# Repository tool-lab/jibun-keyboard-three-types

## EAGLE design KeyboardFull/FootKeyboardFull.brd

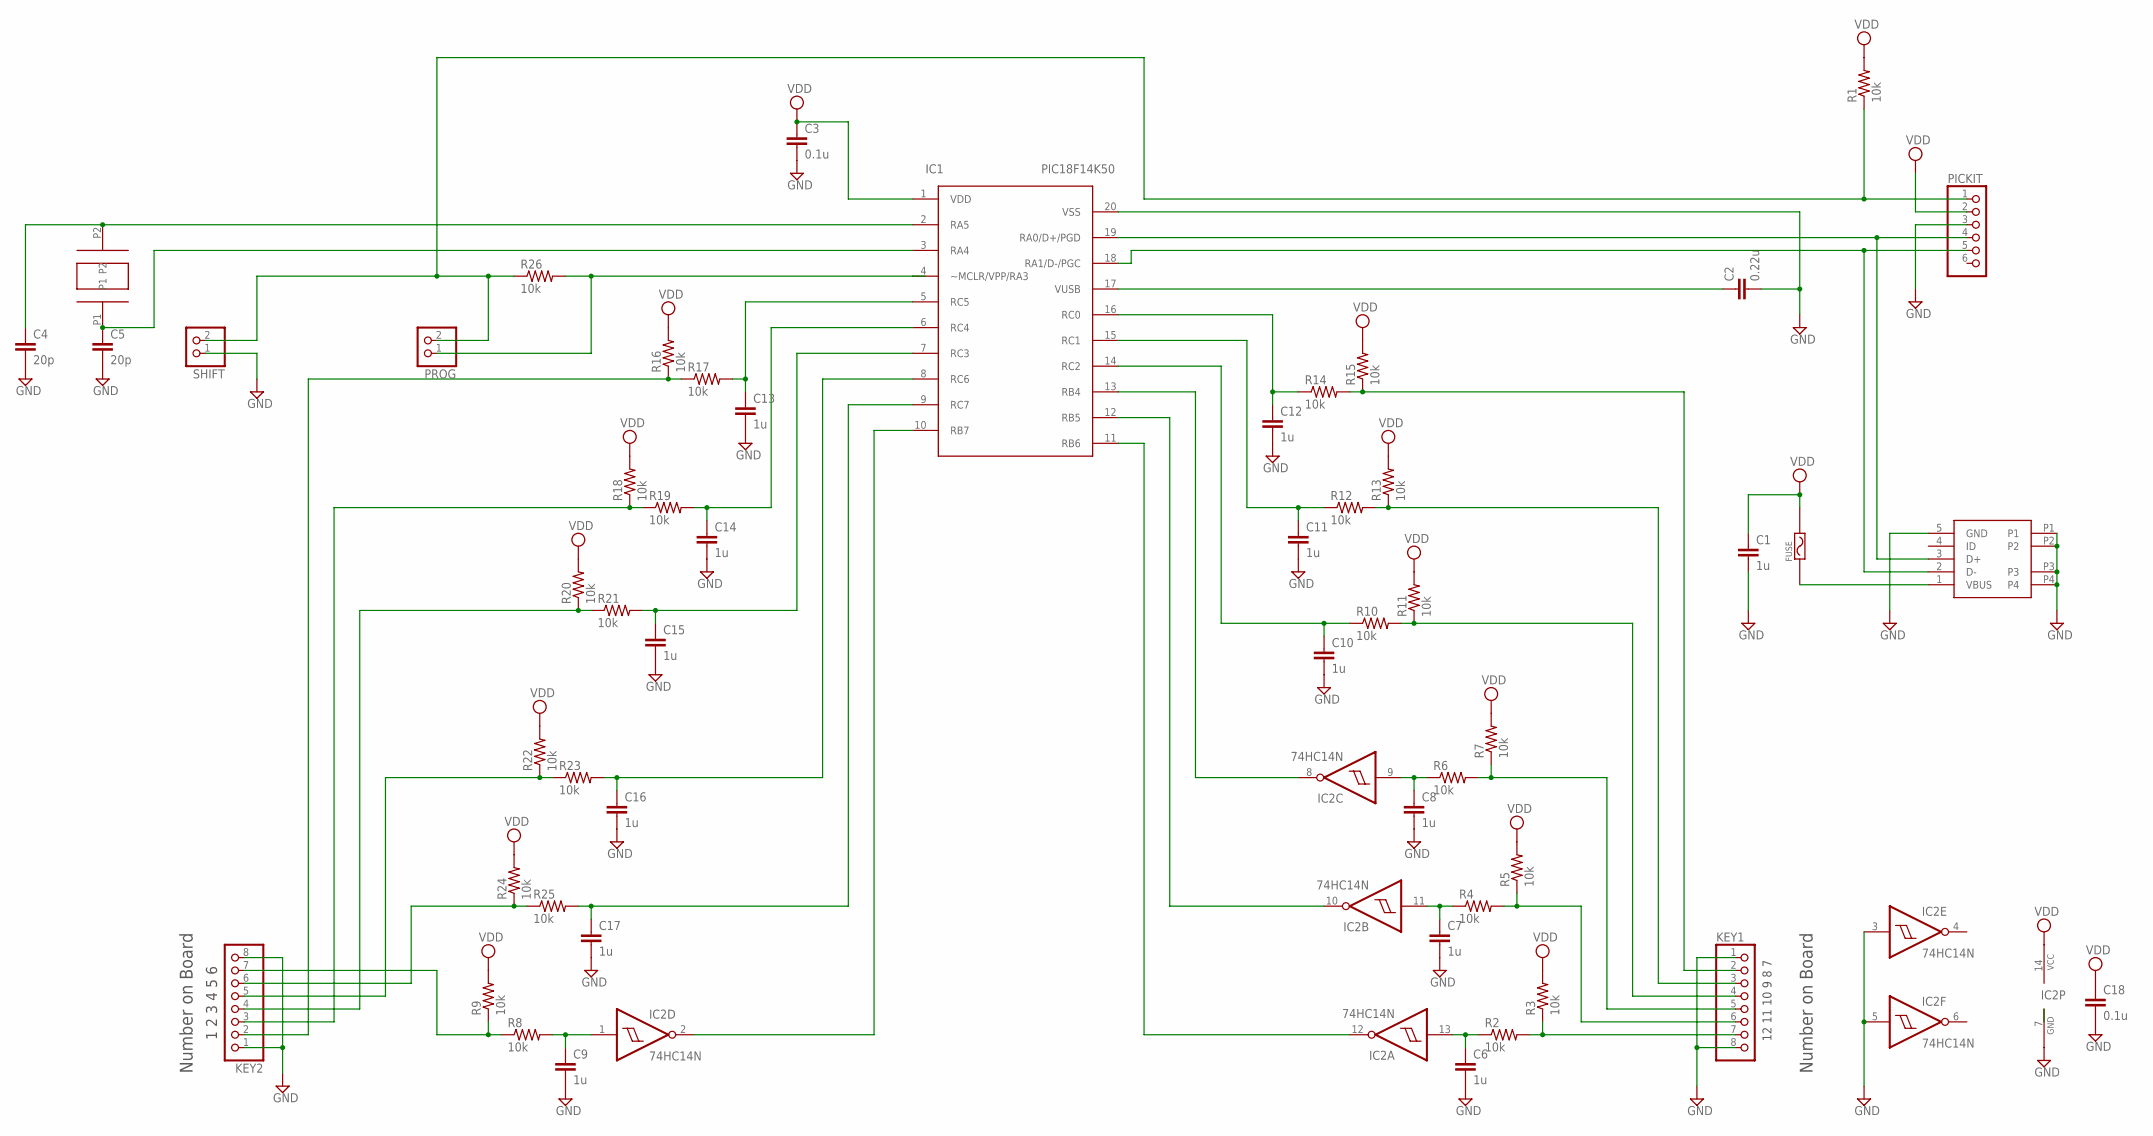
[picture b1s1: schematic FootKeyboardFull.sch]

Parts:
C1, C6, C7, C8, C9, C10, C11, C12, C13, C14, C15, C16, C17: 1u; C025-025X050
C2: 0.22u; C025-025X050
C3, C18: 0.1u; C025-025X050
C4, C5: 20p; C025-025X050
FUSE: POLYSWITCH/3025; SMD/30X25
IC1: PIC18F14K50; DIL20
IC2: 74HC14N; DIL14
KEY1, KEY2: PINHD-1X8; 1X08
PICKIT: PINHD-1X6; 1X06
PROG: PINHD-1X2; 1X02
R1, R2, R3, R4, R5, R6, R7, R8, R9, R10, R11, R12, R13, R14, R15, R16, R17, R18, R19, R20, R21, R22, R23, R24, R25, R26: 10k; 0204/7
SHIFT: PINHD-1X2; 1X02
USB: AKIZUKI-USB-MINI-B
XTAL: 12M; AKIZUKI-XTAL

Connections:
GND: C1.2, C2.2, C3.2, C4.2, C5.2, C6.2, C7.2, C8.2, C9.2, C10.2, C11.2, C12.2, C13.2, C14.2, C15.2, C16.2, C17.2, C18.2, IC1.20 (VSS), IC2.3 (I), IC2.5 (I), IC2.7 (GND), KEY1.1, KEY1.8, KEY2.1, KEY2.8, PICKIT.3, SHIFT.1, USB.5 (GND), USB.P1, USB.P2, USB.P3, USB.P4
unnamed: IC1.19 (RA0/D+/PGD), PICKIT.4, USB.3 (D+)
unnamed: C5.1, IC1.3 (RA4), XTAL.P1
unnamed: C4.1, IC1.2 (RA5), XTAL.P2
unnamed: IC1.18 (RA1/D-/PGC), PICKIT.5, USB.2 (D-)
unnamed: C6.1, IC2.13 (I), R2.1
unnamed: FUSE.P1, USB.1 (VBUS)
unnamed: KEY1.7, R2.2, R3.1
unnamed: C2.1, IC1.17 (VUSB)
unnamed: C8.1, IC2.9 (I), R6.1
unnamed: C7.1, IC2.11 (I), R4.1
unnamed: KEY1.6, R4.2, R5.1
unnamed: KEY1.5, R6.2, R7.1
unnamed: C9.1, IC2.1 (I), R8.2
unnamed: KEY2.7, R8.1, R9.1
unnamed: C10.1, IC1.14 (RC2), R10.1
unnamed: KEY1.4, R10.2, R11.1
unnamed: C11.1, IC1.15 (RC1), R12.1
unnamed: KEY1.3, R12.2, R13.1
unnamed: C12.1, IC1.16 (RC0), R14.1
unnamed: KEY1.2, R14.2, R15.1
unnamed: KEY2.2, R16.1, R17.1
unnamed: C13.1, IC1.5 (RC5), R17.2
unnamed: IC1.13 (RB4), IC2.8 (O)
unnamed: IC1.12 (RB5), IC2.10 (O)
unnamed: IC1.11 (RB6), IC2.12 (O)
unnamed: KEY2.3, R18.1, R19.1
unnamed: C14.1, IC1.6 (RC4), R19.2
unnamed: KEY2.4, R20.1, R21.1
unnamed: C15.1, IC1.7 (RC3), R21.2
unnamed: KEY2.5, R22.1, R23.1
unnamed: C16.1, IC1.8 (RC6), R23.2
unnamed: KEY2.6, R24.1, R25.1
unnamed: C17.1, IC1.9 (RC7), R25.2
unnamed: PICKIT.1, PROG.2, R1.1, R26.1, SHIFT.2
unnamed: IC1.4 (~MCLR/VPP/RA3), PROG.1, R26.2
unnamed: IC1.10 (RB7), IC2.2 (O)
VDD: C1.1, C3.1, C18.1, FUSE.P2, IC1.1 (VDD), IC2.14 (VCC), PICKIT.2, R1.2, R3.2, R5.2, R7.2, R9.2, R11.2, R13.2, R15.2, R16.2, R18.2, R20.2, R22.2, R24.2

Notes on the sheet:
Number on Board
1 2 3 4 5 6
12 11 10 9 8 7

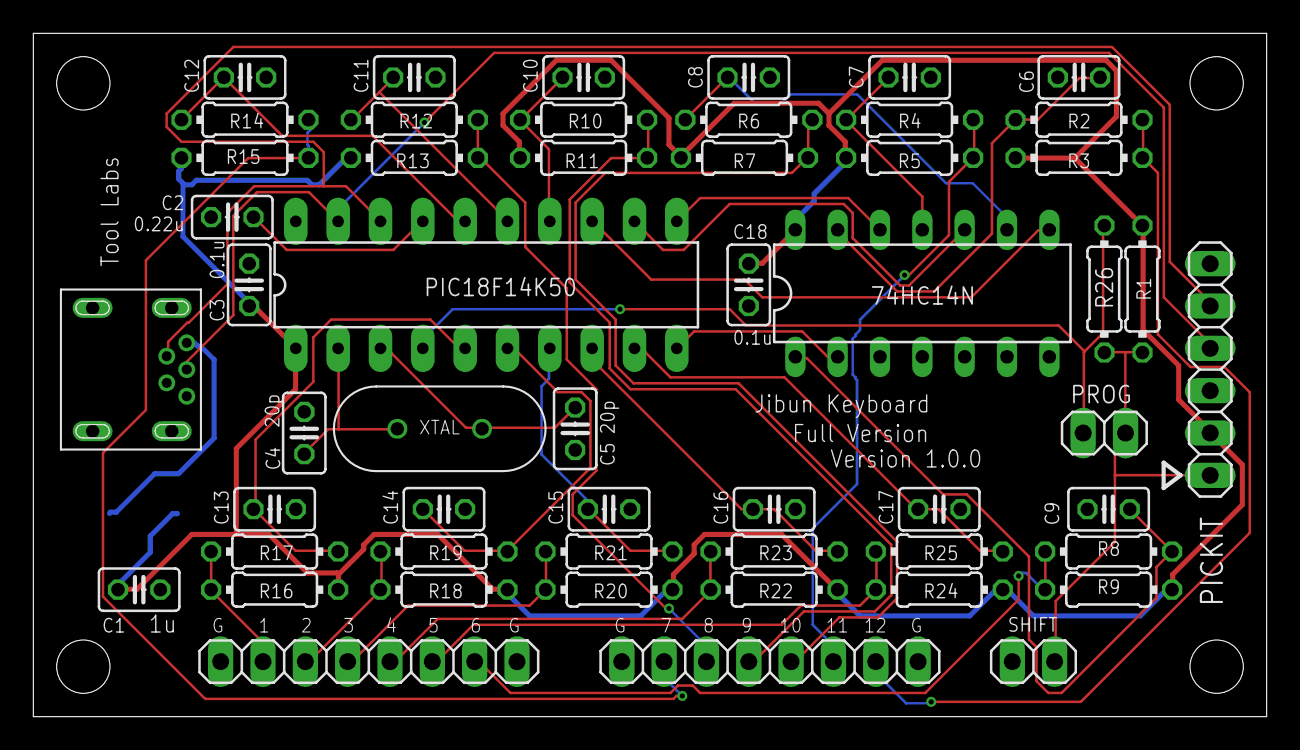
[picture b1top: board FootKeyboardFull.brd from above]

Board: 2 copper layers, 74.0 x 41.0 mm, 54 parts (1 on the bottom side), 38 nets.

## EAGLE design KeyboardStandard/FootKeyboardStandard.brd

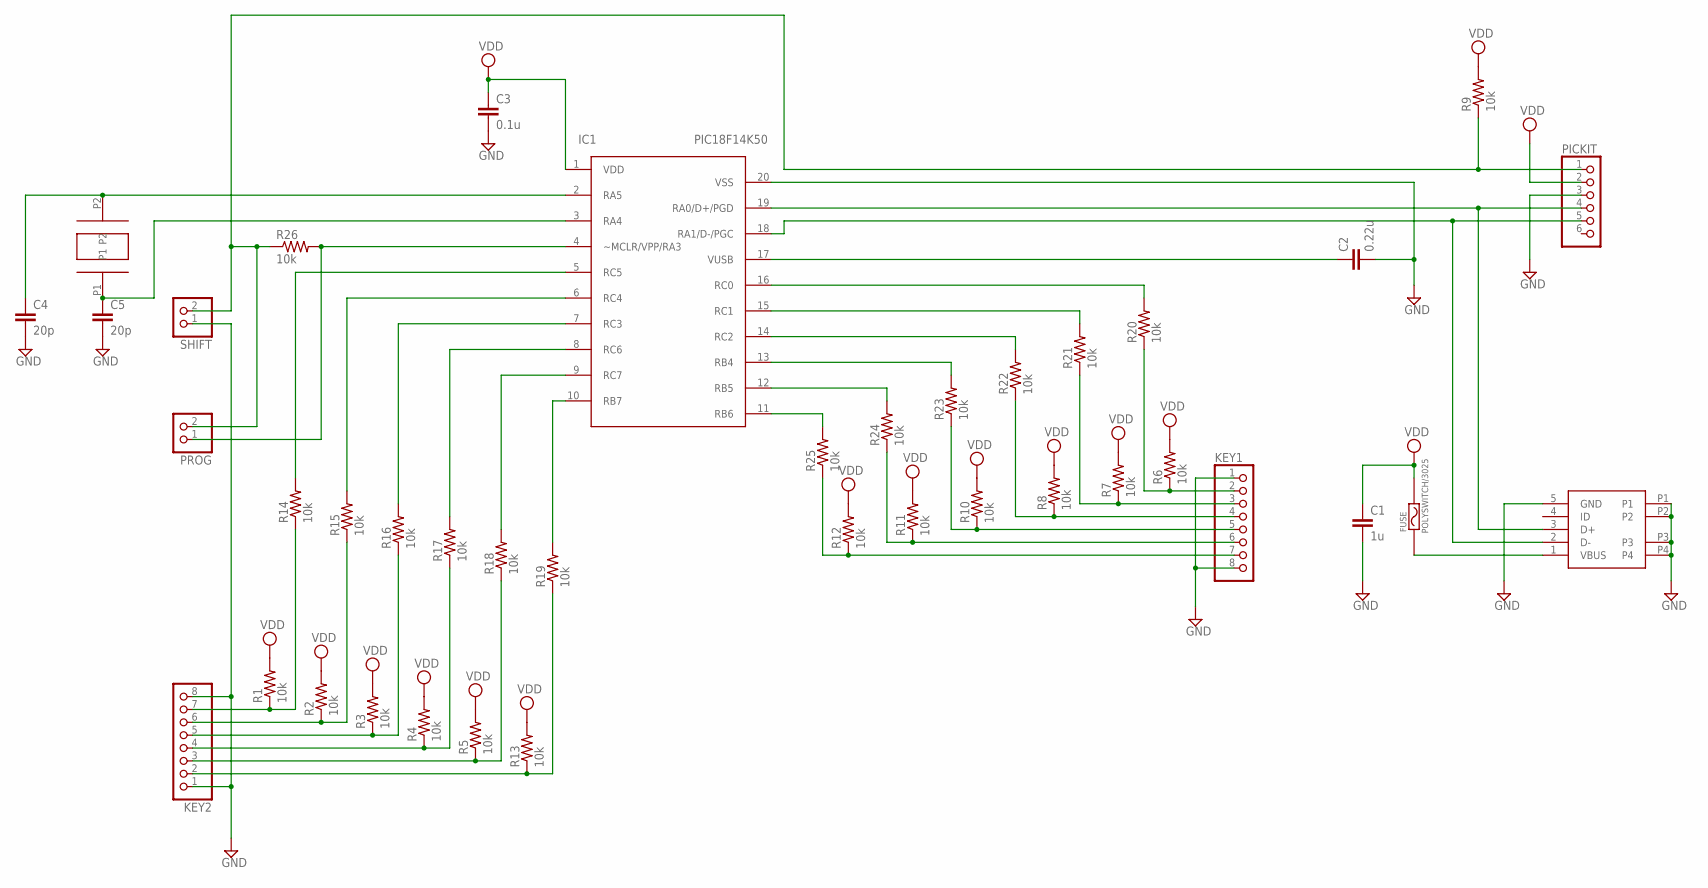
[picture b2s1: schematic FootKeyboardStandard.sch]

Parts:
C1: 1u; C025-025X050
C2: 0.22u; C025-025X050
C3: 0.1u; C025-025X050
C4, C5: 20p; C025-025X050
FUSE: POLYSWITCH/3025; SMD/30X25
IC1: PIC18F14K50; DIL20
KEY1, KEY2: PINHD-1X8; 1X08
PICKIT: PINHD-1X6; 1X06
PROG: PINHD-1X2; 1X02
R1, R2, R3, R4, R5, R6, R7, R8, R9, R10, R11, R12, R13, R14, R15, R16, R17, R18, R19, R20, R21, R22, R23, R24, R25, R26: 10k; 0204/7
SHIFT: PINHD-1X2; 1X02
USB: AKIZUKI-USB-MINI-B
XTAL: 12M; AKIZUKI-XTAL

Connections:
GND: C1.2, C2.2, C3.2, C4.2, C5.2, IC1.20 (VSS), KEY1.1, KEY1.8, KEY2.1, KEY2.8, PICKIT.3, SHIFT.1, USB.5 (GND), USB.P1, USB.P2, USB.P3, USB.P4
unnamed: IC1.19 (RA0/D+/PGD), PICKIT.4, USB.3 (D+)
unnamed: C5.1, IC1.3 (RA4), XTAL.P1
unnamed: C4.1, IC1.2 (RA5), XTAL.P2
unnamed: IC1.18 (RA1/D-/PGC), PICKIT.5, USB.2 (D-)
unnamed: IC1.10 (RB7), R19.2
unnamed: FUSE.P1, USB.1 (VBUS)
unnamed: IC1.9 (RC7), R18.2
unnamed: C2.1, IC1.17 (VUSB)
unnamed: KEY2.5, R3.1, R16.1
unnamed: KEY2.4, R4.1, R17.1
unnamed: KEY2.3, R5.1, R18.1
unnamed: KEY2.2, R13.1, R19.1
unnamed: KEY2.7, R1.1, R14.1
unnamed: KEY2.6, R2.1, R15.1
unnamed: IC1.8 (RC6), R17.2
unnamed: IC1.16 (RC0), R20.2
unnamed: IC1.15 (RC1), R21.2
unnamed: IC1.14 (RC2), R22.2
unnamed: KEY1.5, R10.1, R23.1
unnamed: KEY1.6, R11.1, R24.1
unnamed: KEY1.7, R12.1, R25.1
unnamed: IC1.7 (RC3), R16.2
unnamed: IC1.6 (RC4), R15.2
unnamed: IC1.5 (RC5), R14.2
unnamed: KEY1.2, R6.1, R20.1
unnamed: KEY1.3, R7.1, R21.1
unnamed: KEY1.4, R8.1, R22.1
unnamed: IC1.13 (RB4), R23.2
unnamed: IC1.12 (RB5), R24.2
unnamed: IC1.11 (RB6), R25.2
unnamed: PICKIT.1, PROG.2, R9.1, R26.1, SHIFT.2
unnamed: IC1.4 (~MCLR/VPP/RA3), PROG.1, R26.2
VDD: C1.1, C3.1, FUSE.P2, IC1.1 (VDD), PICKIT.2, R1.2, R2.2, R3.2, R4.2, R5.2, R6.2, R7.2, R8.2, R9.2, R10.2, R11.2, R12.2, R13.2

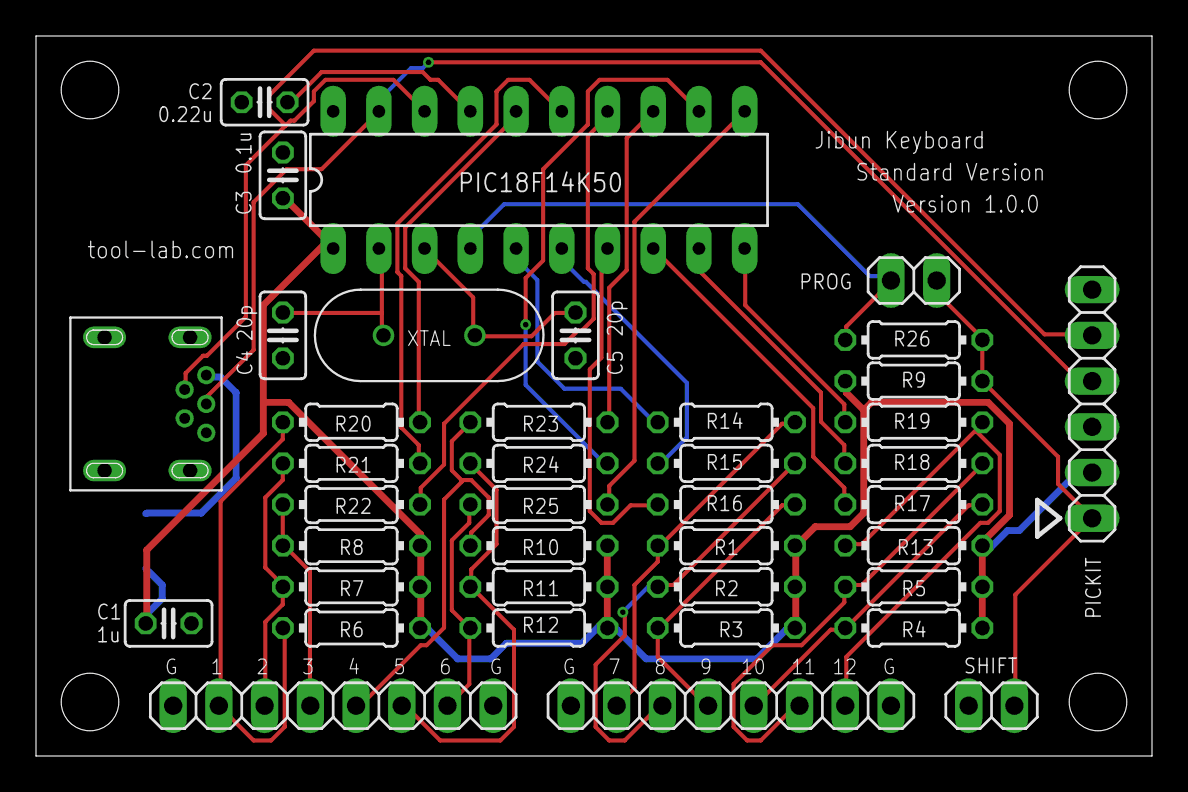
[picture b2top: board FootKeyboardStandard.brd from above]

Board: 2 copper layers, 62.0 x 40.0 mm, 40 parts (1 on the bottom side), 34 nets.

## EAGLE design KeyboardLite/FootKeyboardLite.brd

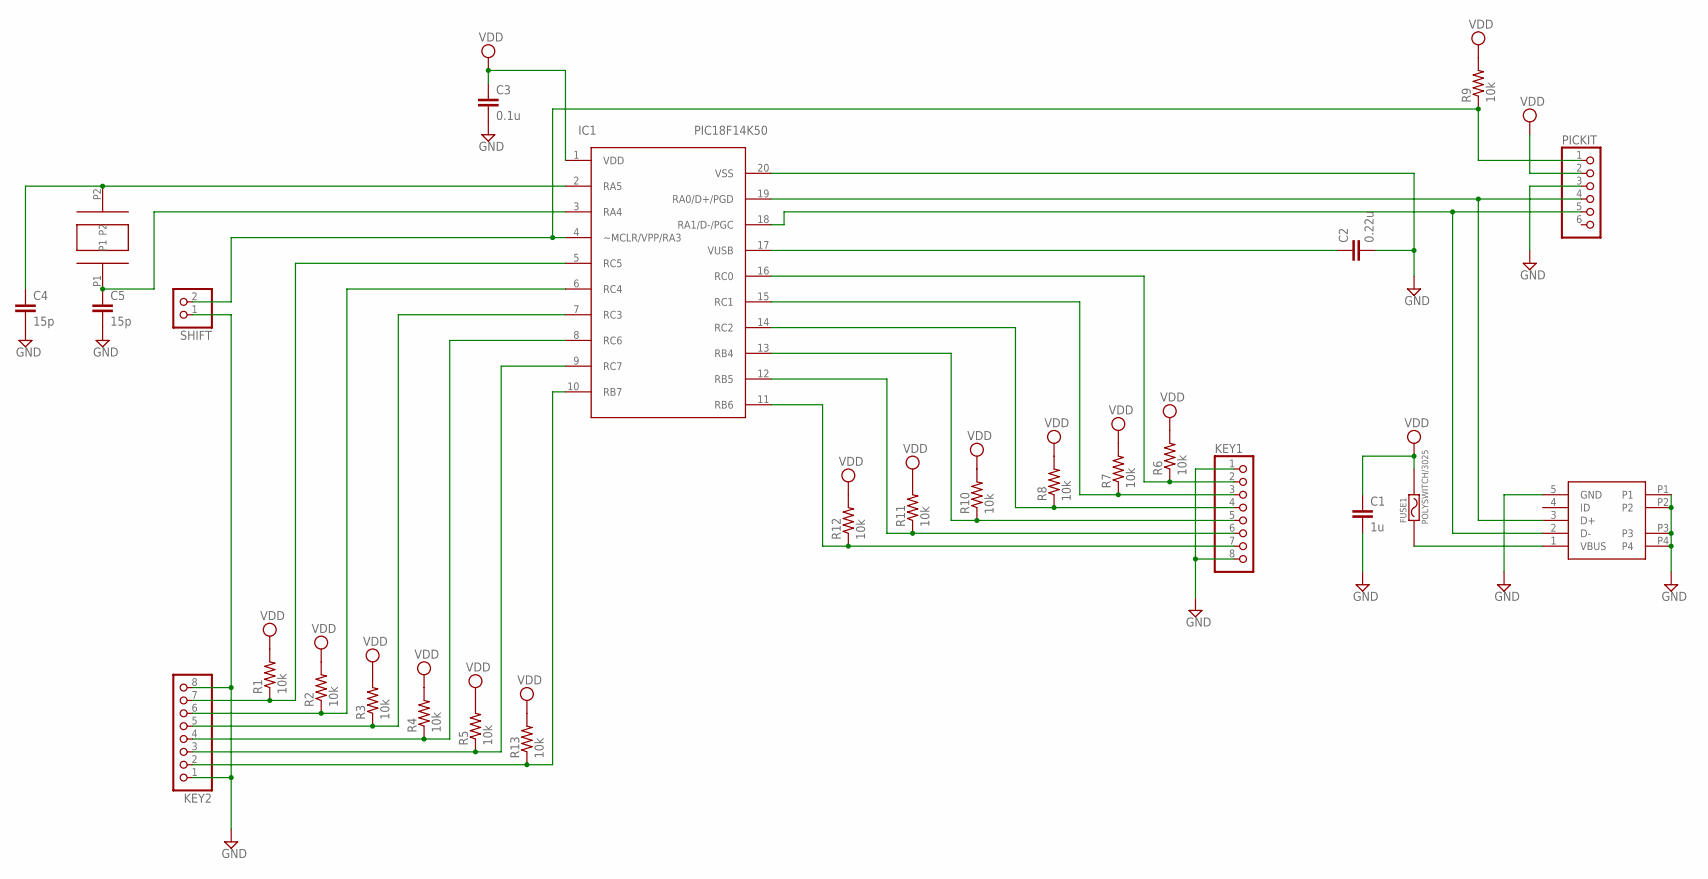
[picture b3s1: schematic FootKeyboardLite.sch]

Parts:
C1: 1u; C025-025X050
C2: 0.22u; C025-025X050
C3: 0.1u; C025-025X050
C4, C5: 15p; C025-025X050
FUSE1: POLYSWITCH/3025; SMD/30X25
IC1: PIC18F14K50; DIL20
KEY1, KEY2: PINHD-1X8; 1X08
PICKIT: PINHD-1X6; 1X06
R1, R2, R3, R4, R5, R6, R7, R8, R9, R10, R11, R12, R13: 10k; 0204/7
SHIFT: PINHD-1X2; 1X02
USB: AKIZUKI-USB-MINI-B
XTAL: 12M; AKIZUKI-XTAL

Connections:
GND: C1.2, C2.2, C3.2, C4.2, C5.2, IC1.20 (VSS), KEY1.1, KEY1.8, KEY2.1, KEY2.8, PICKIT.3, SHIFT.1, USB.5 (GND), USB.P1, USB.P2, USB.P3, USB.P4
unnamed: IC1.19 (RA0/D+/PGD), PICKIT.4, USB.3 (D+)
unnamed: C5.1, IC1.3 (RA4), XTAL.P1
unnamed: C4.1, IC1.2 (RA5), XTAL.P2
unnamed: IC1.18 (RA1/D-/PGC), PICKIT.5, USB.2 (D-)
unnamed: IC1.5 (RC5), KEY2.7, R1.1
unnamed: FUSE1.P1, USB.1 (VBUS)
unnamed: IC1.6 (RC4), KEY2.6, R2.1
unnamed: IC1.4 (~MCLR/VPP/RA3), PICKIT.1, R9.1, SHIFT.2
unnamed: C2.1, IC1.17 (VUSB)
unnamed: IC1.7 (RC3), KEY2.5, R3.1
unnamed: IC1.8 (RC6), KEY2.4, R4.1
unnamed: IC1.9 (RC7), KEY2.3, R5.1
unnamed: IC1.10 (RB7), KEY2.2, R13.1
unnamed: IC1.16 (RC0), KEY1.2, R6.1
unnamed: IC1.15 (RC1), KEY1.3, R7.1
unnamed: IC1.14 (RC2), KEY1.4, R8.1
unnamed: IC1.13 (RB4), KEY1.5, R10.1
unnamed: IC1.12 (RB5), KEY1.6, R11.1
unnamed: IC1.11 (RB6), KEY1.7, R12.1
VDD: C1.1, C3.1, FUSE1.P2, IC1.1 (VDD), PICKIT.2, R1.2, R2.2, R3.2, R4.2, R5.2, R6.2, R7.2, R8.2, R9.2, R10.2, R11.2, R12.2, R13.2

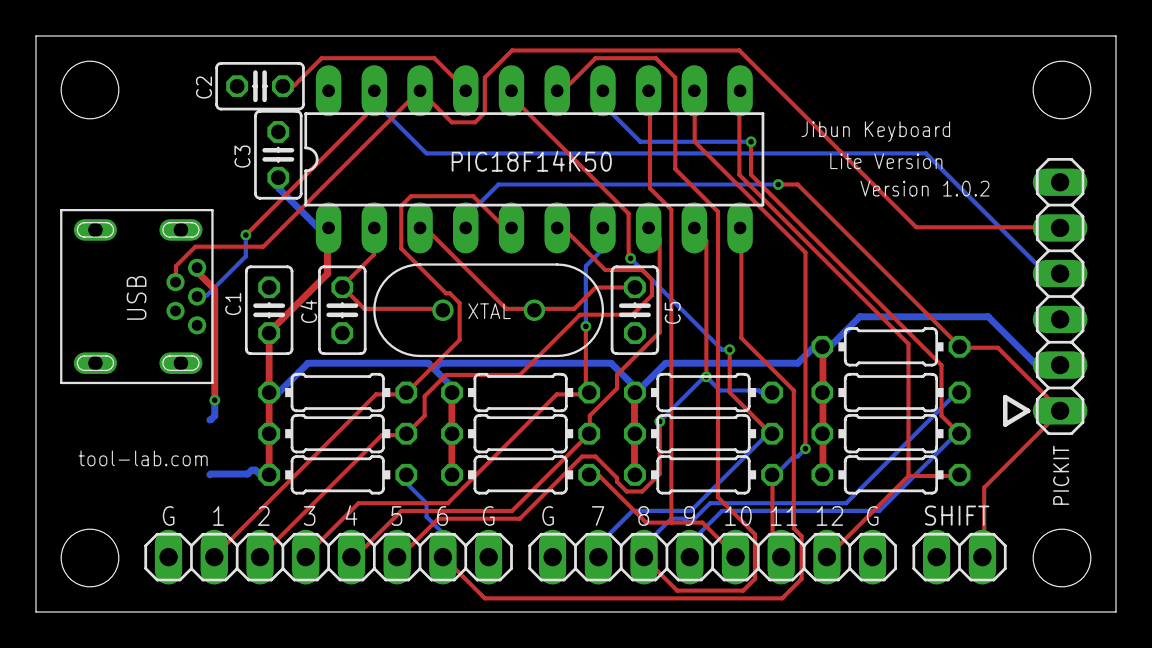
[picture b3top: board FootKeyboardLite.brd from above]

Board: 2 copper layers, 60.0 x 32.0 mm, 26 parts (1 on the bottom side), 21 nets.
